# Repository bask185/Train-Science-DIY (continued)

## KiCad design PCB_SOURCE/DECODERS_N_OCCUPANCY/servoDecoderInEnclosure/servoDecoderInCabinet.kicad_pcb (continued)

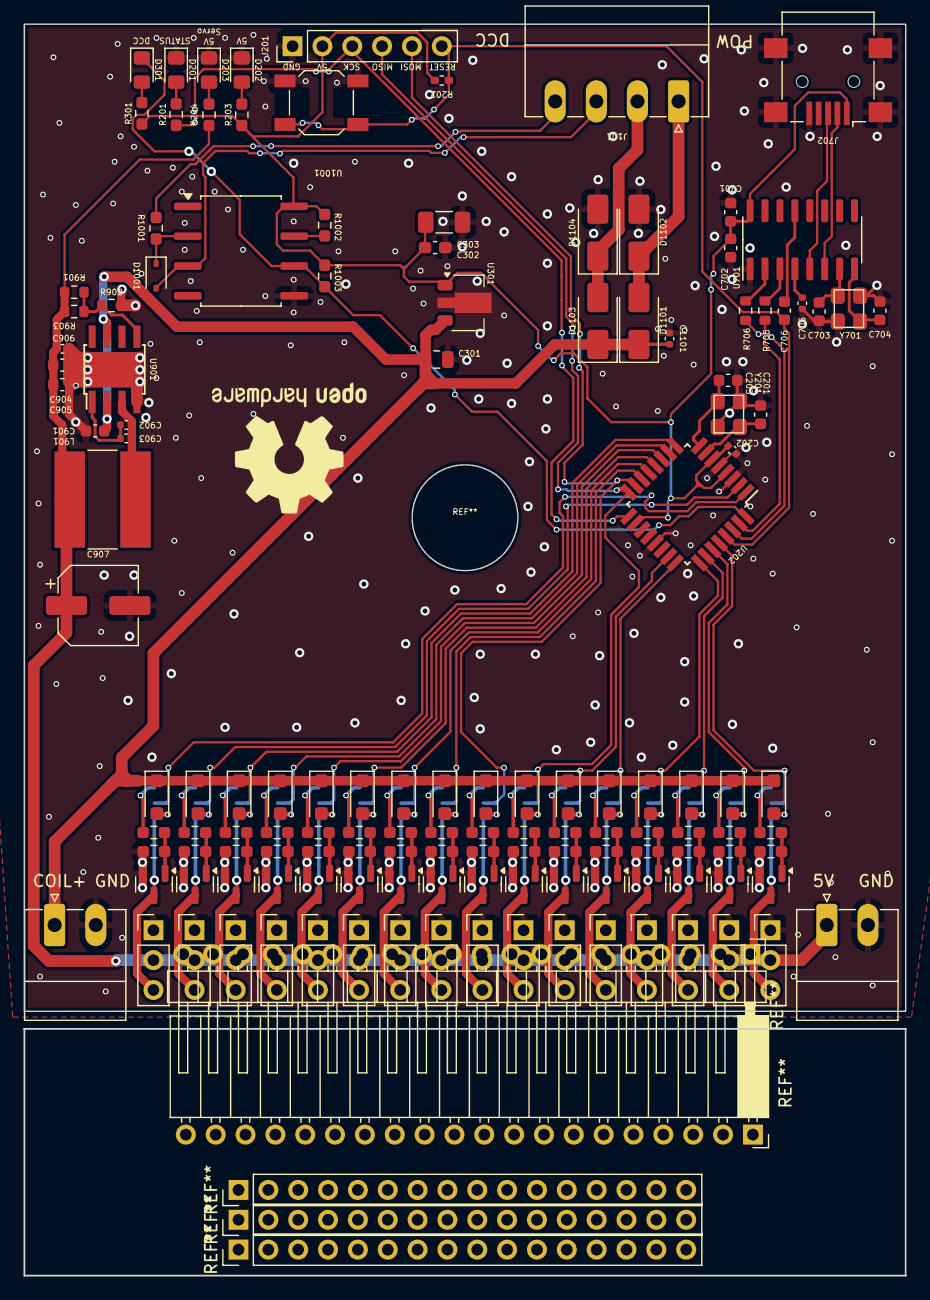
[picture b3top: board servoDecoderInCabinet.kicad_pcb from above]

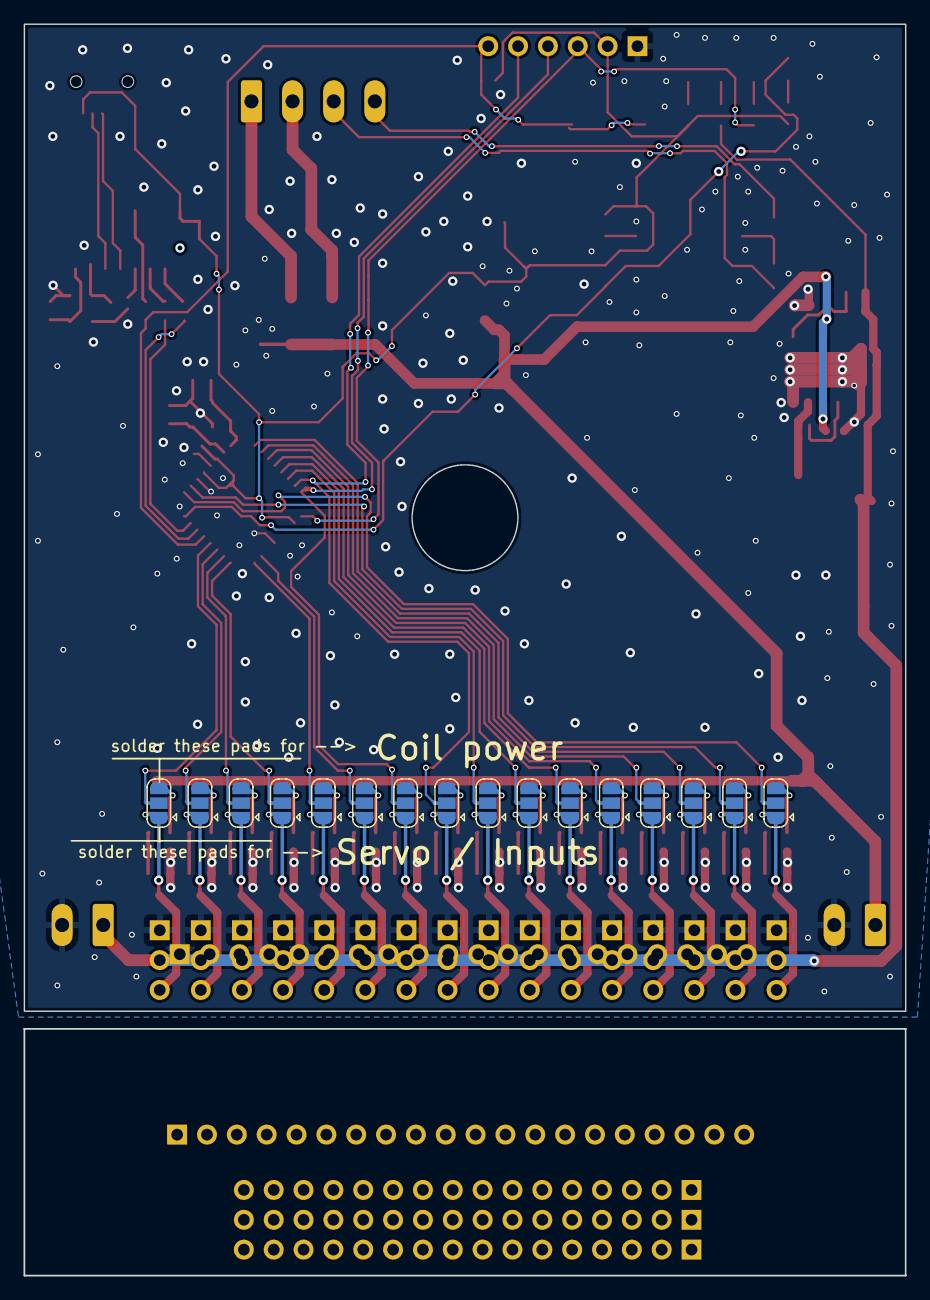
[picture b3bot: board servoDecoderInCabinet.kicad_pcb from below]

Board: 2 copper layers, 75.0 x 106.5 mm, 152 parts (16 on the bottom side), 96 nets.

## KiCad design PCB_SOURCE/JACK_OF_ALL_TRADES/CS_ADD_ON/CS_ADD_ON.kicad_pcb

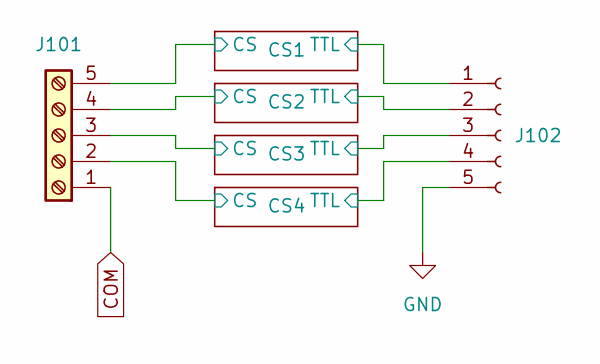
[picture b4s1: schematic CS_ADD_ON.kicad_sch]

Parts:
J101: Screw_Terminal_01x05; TerminalBlock_Phoenix_MKDS-1,5-5-5.08_1x05_P5.08mm_Horizont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
J102: Conn_01x05_Socket; PinSocket_1x05_P2.54mm_Horizontal

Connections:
/CS1/CS: J101.5; also elsewhere on the board
/CS1/TTL: J102.1; also elsewhere on the board
/CS2/CS: J101.4; also elsewhere on the board
/CS2/TTL: J102.2; also elsewhere on the board
/CS3/CS: J101.3; also elsewhere on the board
/CS3/TTL: J102.3; also elsewhere on the board
/CS4/CS: J101.2; also elsewhere on the board
/CS4/TTL: J102.4; also elsewhere on the board
COM: J101.1; also elsewhere on the board
GND: J102.5; also elsewhere on the board

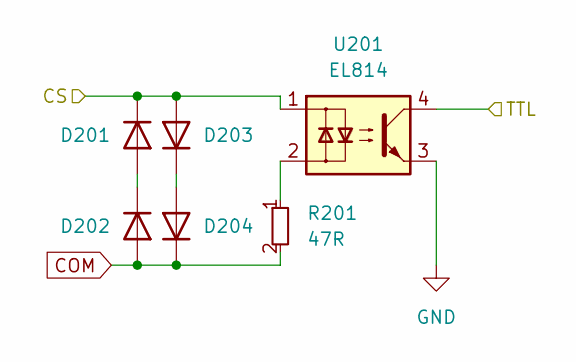
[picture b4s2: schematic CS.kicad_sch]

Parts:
D201, D202, D203, D204: SS53; D_SMA; JLCPCB Part# C8678
R201: 47R; R_0603_smalltext; JLCPCB Part# C23182
U201: EL814; SMDIP-4_W9.53mm; JLCPCB Part# C500388

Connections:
/CS1/CS: D201.1 (K), D203.2 (A), U201.1; also elsewhere on the board
/CS1/TTL: U201.4; also elsewhere on the board
COM: D202.2 (A), D204.1 (K), R201.2; also elsewhere on the board
GND: U201.3; also elsewhere on the board
unnamed: D201.2 (A), D202.1 (K)
unnamed: D203.1 (K), D204.2 (A)
unnamed: R201.1, U201.2

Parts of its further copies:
D301, D302, D303, D304, D401, D402, D403, D404, D501, D502, D503, D504: SS53; D_SMA; JLCPCB Part# C8678
R301, R401, R501: 47R; R_0603_smalltext; JLCPCB Part# C23182
U301, U401, U501: EL814; SMDIP-4_W9.53mm; JLCPCB Part# C500388

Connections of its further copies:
/CS2/CS: D301.1 (K), D303.2 (A), U301.1; also elsewhere on the board
/CS2/TTL: U301.4; also elsewhere on the board
/CS3/CS: D401.1 (K), D403.2 (A), U401.1; also elsewhere on the board
/CS3/TTL: U401.4; also elsewhere on the board
/CS4/CS: D501.1 (K), D503.2 (A), U501.1; also elsewhere on the board
/CS4/TTL: U501.4; also elsewhere on the board
COM: D302.2 (A), D304.1 (K), D402.2 (A), D404.1 (K), D502.2 (A), D504.1 (K), R301.2, R401.2, R501.2; also elsewhere on the board
GND: U301.3, U401.3, U501.3; also elsewhere on the board
unnamed: D301.2 (A), D302.1 (K)
unnamed: D303.1 (K), D304.2 (A)
unnamed: D401.2 (A), D402.1 (K)
unnamed: D403.1 (K), D404.2 (A)
unnamed: D501.2 (A), D502.1 (K)
unnamed: D503.1 (K), D504.2 (A)
unnamed: R301.1, U301.2
unnamed: R401.1, U401.2
unnamed: R501.1, U501.2

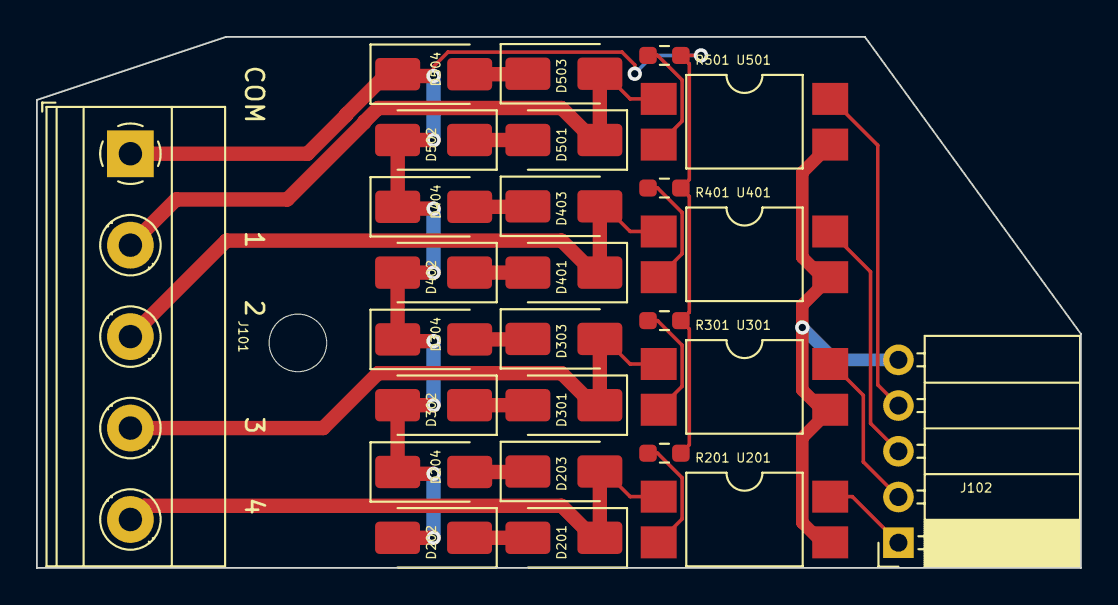
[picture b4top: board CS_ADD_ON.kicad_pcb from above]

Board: 2 copper layers, 58.0 x 29.5 mm, 26 parts (0 on the bottom side), 22 nets.

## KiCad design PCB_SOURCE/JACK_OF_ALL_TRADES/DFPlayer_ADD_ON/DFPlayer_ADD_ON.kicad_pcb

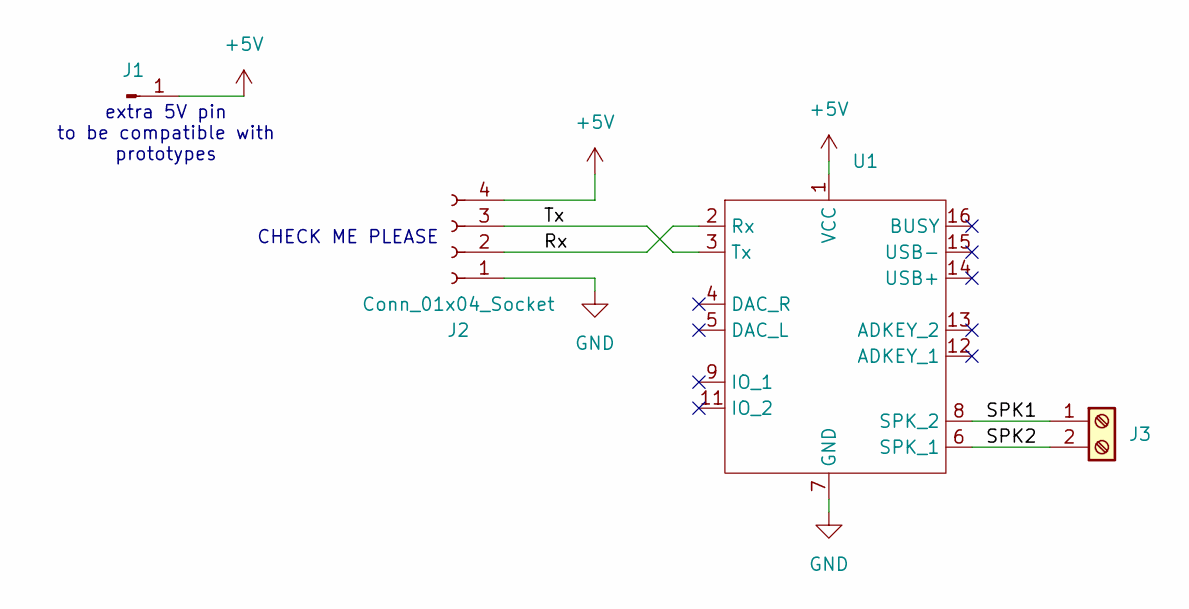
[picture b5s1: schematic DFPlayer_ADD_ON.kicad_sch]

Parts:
J1: Conn_01x01_Pin; PinHeader_1x01_P2.54mm_Vertical
J2: Conn_01x04_Socket; PinSocket_1x04_P2.54mm_Horizontal
J3: Screw_Terminal_01x02; PhoenixContact_MC_1,5_2-G-3.5_1x02_P3.50mm_Horizontal
U1: DFPlayer

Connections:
+5V: J1.1, J2.4, U1.1 (VCC)
/Rx: J2.2, U1.2 (Rx)
/SPK1: J3.1, U1.8 (SPK_2)
/SPK2: J3.2, U1.6 (SPK_1)
/Tx: J2.3, U1.3 (Tx)
GND: J2.1, U1.7 (GND), U1.10 (GND)

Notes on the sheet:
CHECK ME PLEASE
extra 5V pin to be compatible with prototypes

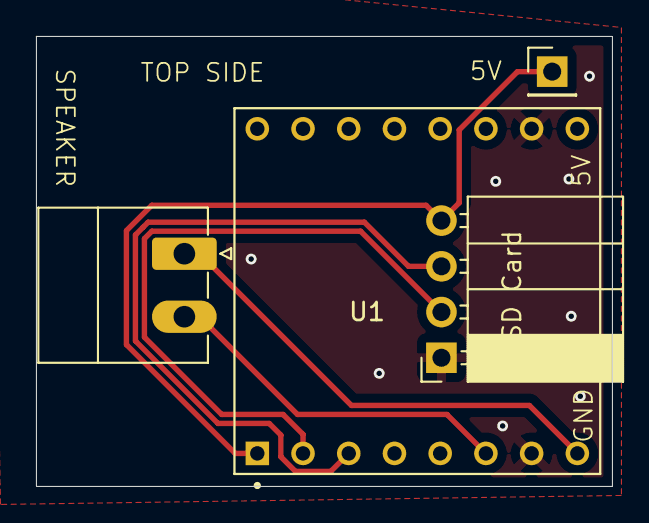
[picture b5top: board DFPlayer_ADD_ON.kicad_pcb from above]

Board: 2 copper layers, 32.0 x 25.0 mm, 4 parts (0 on the bottom side), 6 nets.

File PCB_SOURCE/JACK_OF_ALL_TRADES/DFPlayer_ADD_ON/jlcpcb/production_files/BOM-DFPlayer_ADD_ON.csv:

Comment,Designator,Footprint,LCSC
~,U1,DFPlayer,
Screw_Terminal_01x02,J3,"PhoenixContact_MC_1,5_2-G-3.5_1x02_P3.50mm_Horizontal",
Conn_01x04_Socket,J2,PinSocket_1x04_P2.54mm_Horizontal,
Conn_01x01_Pin,J1,PinHeader_1x01_P2.54mm_Vertical,

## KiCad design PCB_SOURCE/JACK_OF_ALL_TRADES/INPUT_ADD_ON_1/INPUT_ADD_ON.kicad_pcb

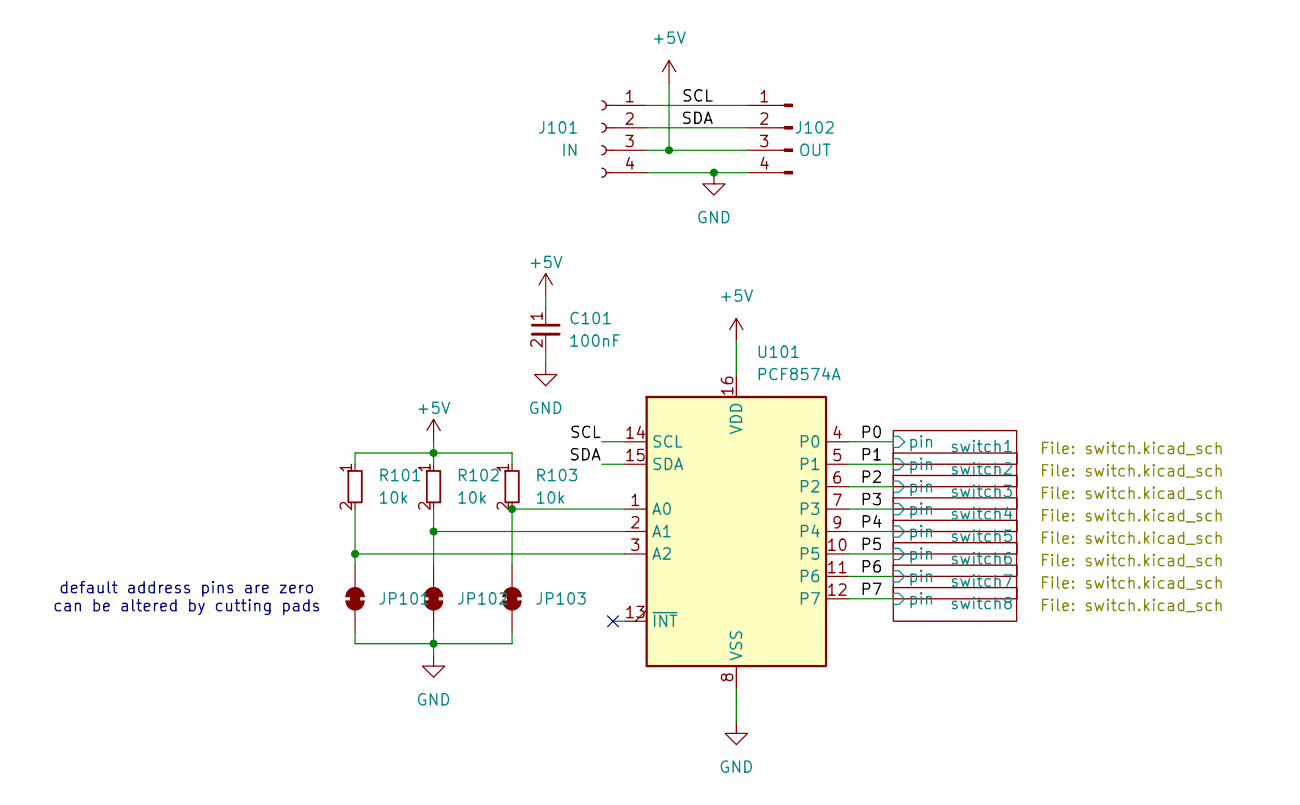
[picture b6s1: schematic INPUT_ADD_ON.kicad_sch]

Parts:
C101: 100nF; C_0603_1608Metric; JLCPCB Part# C14663
J101: IN; PinSocket_1x04_P2.54mm_Horizontal
J102: OUT; PinHeader_1x04_P2.54mm_Horizontal
JP101, JP102, JP103: SolderJumper_2_Bridged; SolderJumper-2_P1.3mm_Bridged_RoundedPad1.0x1.5mm
R101, R102, R103: 10k; R_0603_smalltext; JLCPCB Part# C25804
U101: PCF8574A; SOP-16_4.55x10.3mm_P1.27mm; JLCPCB Part# C2987288

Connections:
+5V: C101.1, J101.3, J102.3, R101.1, R102.1, R103.1, U101.16 (VDD); also elsewhere on the board
/P0: U101.4 (P0); also elsewhere on the board
/P1: U101.5 (P1); also elsewhere on the board
/P2: U101.6 (P2); also elsewhere on the board
/P3: U101.7 (P3); also elsewhere on the board
/P4: U101.9 (P4); also elsewhere on the board
/P5: U101.10 (P5); also elsewhere on the board
/P6: U101.11 (P6); also elsewhere on the board
/P7: U101.12 (P7); also elsewhere on the board
/SCL: J101.1, J102.1, U101.14 (SCL)
/SDA: J101.2, J102.2, U101.15 (SDA)
GND: C101.2, J101.4, J102.4, JP101.1 (A), JP102.1 (A), JP103.1 (A), U101.8 (VSS); also elsewhere on the board
unnamed: JP101.2 (B), R101.2, U101.3 (A2)
unnamed: JP102.2 (B), R102.2, U101.2 (A1)
unnamed: JP103.2 (B), R103.2, U101.1 (A0)

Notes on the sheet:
default address pins are zero can be altered by cutting pads

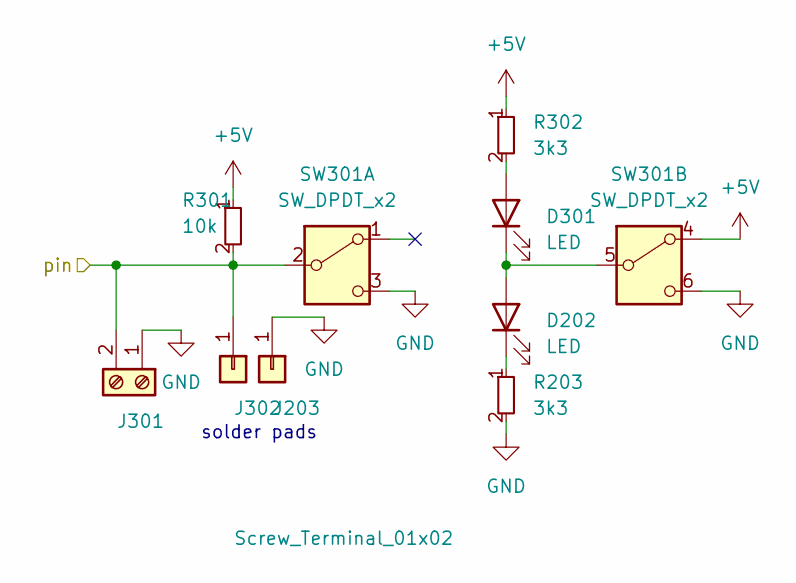
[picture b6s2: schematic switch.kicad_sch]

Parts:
D202, D301: LED; LED_D3.0mm
J203, J302: Conn_01x01; SolderWirePad_1x01_SMD_1x2mm
J301: Screw_Terminal_01x02; TerminalBlock_Xinya_XY308-2.54-2P_1x02_P2.54mm_Horizontal
R203, R302: 3k3; R_0805_handsolder-smalltext; JLCPCB Part# C26010
R301: 10k; R_0603_smalltext; JLCPCB Part# C25804
SW301: SW_DPDT_x2; MTS_DPDT

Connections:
+5V: R301.1, R302.1, SW301.4 (A); also elsewhere on the board
/P1: J301.2, J302.1, R301.2, SW301.2 (B); also elsewhere on the board
GND: J203.1, J301.1, R203.2, SW301.3 (C), SW301.6 (C); also elsewhere on the board
unnamed: D202.1 (K), R203.1
unnamed: D301.2 (A), R302.2

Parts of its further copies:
D201, D302, D401, D402, D501, D502, D601, D602, D701, D702, D801, D802, D901, D902: LED; LED_D3.0mm
J201, J401, J501, J601, J701, J801, J901: Screw_Terminal_01x02; TerminalBlock_Xinya_XY308-2.54-2P_1x02_P2.54mm_Horizontal
J202, J303, J402, J403, J502, J503, J602, J603, J702, J703, J802, J803, J902, J903: Conn_01x01; SolderWirePad_1x01_SMD_1x2mm
R201, R401, R501, R601, R701, R801, R901: 10k; R_0603_smalltext; JLCPCB Part# C25804
R202, R303, R402, R403, R502, R503, R602, R603, R702, R703, R802, R803, R902, R903: 3k3; R_0805_handsolder-smalltext; JLCPCB Part# C26010
SW201, SW401, SW501, SW601, SW701, SW801, SW901: SW_DPDT_x2; MTS_DPDT

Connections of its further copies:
+5V: R201.1, R202.1, R401.1, R402.1, R501.1, R502.1, R601.1, R602.1, R701.1, R702.1, R801.1, R802.1, R901.1, R902.1, SW201.4 (A), SW401.4 (A), SW501.4 (A), SW601.4 (A), SW701.4 (A), SW801.4 (A), SW901.4 (A); also elsewhere on the board
/P0: J201.2, J202.1, R201.2, SW201.2 (B); also elsewhere on the board
/P2: J401.2, J402.1, R401.2, SW401.2 (B); also elsewhere on the board
/P3: J501.2, J502.1, R501.2, SW501.2 (B); also elsewhere on the board
/P4: J601.2, J602.1, R601.2, SW601.2 (B); also elsewhere on the board
/P5: J701.2, J702.1, R701.2, SW701.2 (B); also elsewhere on the board
/P6: J801.2, J802.1, R801.2, SW801.2 (B); also elsewhere on the board
/P7: J901.2, J902.1, R901.2, SW901.2 (B); also elsewhere on the board
GND: J201.1, J303.1, J401.1, J403.1, J501.1, J503.1, J601.1, J603.1, J701.1, J703.1, J801.1, J803.1, J901.1, J903.1, R303.2, R403.2, R503.2, R603.2, R703.2, R803.2, R903.2, SW201.3 (C), SW201.6 (C), SW401.3 (C), SW401.6 (C), SW501.3 (C), SW501.6 (C), SW601.3 (C), SW601.6 (C), SW701.3 (C), SW701.6 (C), SW801.3 (C), SW801.6 (C), SW901.3 (C), SW901.6 (C); also elsewhere on the board
unnamed: D201.2 (A), R202.2
unnamed: D302.1 (K), R303.1
unnamed: D401.2 (A), R402.2
unnamed: D401.1 (K), D402.2 (A), SW401.5 (B)
unnamed: D402.1 (K), R403.1
unnamed: D501.2 (A), R502.2
unnamed: D501.1 (K), D502.2 (A), SW501.5 (B)
unnamed: D502.1 (K), R503.1
unnamed: D601.2 (A), R602.2
unnamed: D601.1 (K), D602.2 (A), SW601.5 (B)
unnamed: D602.1 (K), R603.1
unnamed: D701.2 (A), R702.2
unnamed: D701.1 (K), D702.2 (A), SW701.5 (B)
unnamed: D702.1 (K), R703.1
unnamed: D801.2 (A), R802.2
unnamed: D801.1 (K), D802.2 (A), SW801.5 (B)
unnamed: D802.1 (K), R803.1
unnamed: D901.2 (A), R902.2
unnamed: D901.1 (K), D902.2 (A), SW901.5 (B)
unnamed: D902.1 (K), R903.1

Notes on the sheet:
solder pads

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
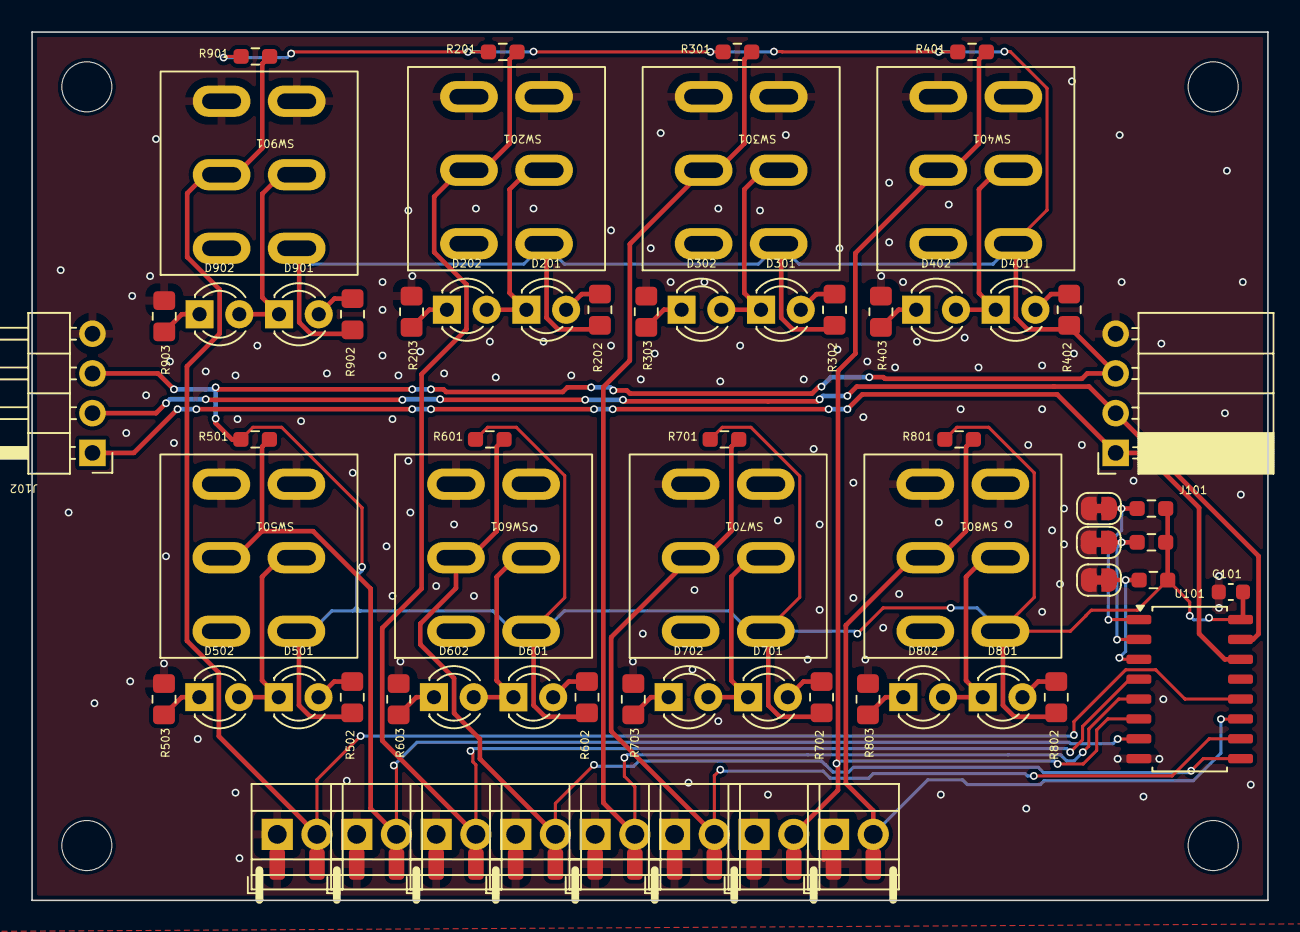
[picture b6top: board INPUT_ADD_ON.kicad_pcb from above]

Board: 2 copper layers, 79.0 x 55.5 mm, 82 parts (0 on the bottom side), 39 nets.

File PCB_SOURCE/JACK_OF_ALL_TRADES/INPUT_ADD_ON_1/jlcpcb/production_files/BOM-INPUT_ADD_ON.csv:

Comment,Designator,Footprint,LCSC
100nF,C101,C_0603_1608Metric,C14663
10k,"R101,R102,R103,R201,R301,R401,R501,R601,R701,R801,R901",R_0603_smalltext,C25804
3k3,"R202,R203,R302,R303,R402,R403,R502,R503,R602,R603,R702,R703,R802,R803,R902,R903",R_0805_handsolder-smalltext,C26010
PCF8574A,U101,SOP-16_4.55x10.3mm_P1.27mm,C2987288
Screw_Terminal_01x02,J901,TerminalBlock_Xinya_XY308-2.54-2P_1x02_P2.54mm_Horizontal,
Screw_Terminal_01x02,J801,TerminalBlock_Xinya_XY308-2.54-2P_1x02_P2.54mm_Horizontal,
Screw_Terminal_01x02,J701,TerminalBlock_Xinya_XY308-2.54-2P_1x02_P2.54mm_Horizontal,
Screw_Terminal_01x02,J601,TerminalBlock_Xinya_XY308-2.54-2P_1x02_P2.54mm_Horizontal,
Screw_Terminal_01x02,J501,TerminalBlock_Xinya_XY308-2.54-2P_1x02_P2.54mm_Horizontal,
Screw_Terminal_01x02,J401,TerminalBlock_Xinya_XY308-2.54-2P_1x02_P2.54mm_Horizontal,
Screw_Terminal_01x02,J301,TerminalBlock_Xinya_XY308-2.54-2P_1x02_P2.54mm_Horizontal,
Screw_Terminal_01x02,J201,TerminalBlock_Xinya_XY308-2.54-2P_1x02_P2.54mm_Horizontal,
SW_DPDT_x2,SW901,MTS_DPDT,
SW_DPDT_x2,SW801,MTS_DPDT,
SW_DPDT_x2,SW701,MTS_DPDT,
SW_DPDT_x2,SW601,MTS_DPDT,
SW_DPDT_x2,SW501,MTS_DPDT,
SW_DPDT_x2,SW401,MTS_DPDT,
SW_DPDT_x2,SW301,MTS_DPDT,
SW_DPDT_x2,SW201,MTS_DPDT,
OUT,J102,PinHeader_1x04_P2.54mm_Horizontal,
IN,J101,PinSocket_1x04_P2.54mm_Horizontal,
LED,D902,LED_D3.0mm,
LED,D901,LED_D3.0mm,
LED,D802,LED_D3.0mm,
LED,D801,LED_D3.0mm,
LED,D702,LED_D3.0mm,
LED,D701,LED_D3.0mm,
LED,D602,LED_D3.0mm,
LED,D601,LED_D3.0mm,
LED,D502,LED_D3.0mm,
LED,D501,LED_D3.0mm,
LED,D402,LED_D3.0mm,
LED,D401,LED_D3.0mm,
LED,D302,LED_D3.0mm,
LED,D301,LED_D3.0mm,
LED,D202,LED_D3.0mm,
LED,D201,LED_D3.0mm,
